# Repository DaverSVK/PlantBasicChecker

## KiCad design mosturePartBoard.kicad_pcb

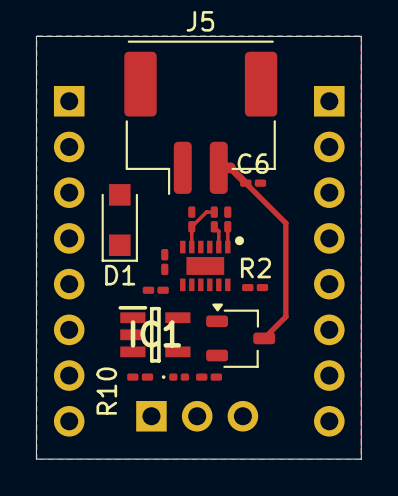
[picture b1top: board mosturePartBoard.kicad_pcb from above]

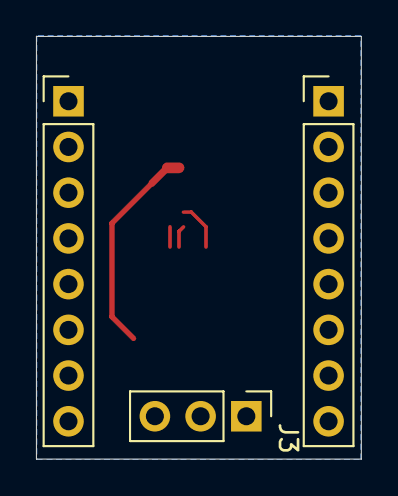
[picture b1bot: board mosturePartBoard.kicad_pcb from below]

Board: 2 copper layers, 18.1 x 23.5 mm, 18 parts (3 on the bottom side), 14 nets.

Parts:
C1, C2: C; C_0201_0603Metric_Pad0.64x0.40mm_HandSolder
C5, C6: 4u7; C_0201_0603Metric_Pad0.64x0.40mm_HandSolder
D1: PMEG2010ER; Nexperia_CFP3_SOD-123W
D3: LED; LED_0201_0603Metric
IC1: MCP73831T-2ACI_OT; SOT95P270X145-5N
J1, J2: Conn_01x08_Pin; PinHeader_1x08_P2.54mm_Vertical
J3: Conn_01x03_Pin; PinHeader_1x03_P2.54mm_Vertical
J5: Conn_01x02_Pin; Molex_CLIK-Mate_502443-0270_1x02-1MP_P2.00mm_Vertical
L1: L; L_0201_0603Metric_Pad0.64x0.40mm_HandSolder
PMV33UPE215: TSOT-23
PS1: TPS62740DSSR; TPS62740
R1: R; R_0201_0603Metric_Pad0.64x0.40mm_HandSolder
R2: 100k; R_0201_0603Metric_Pad0.64x0.40mm_HandSolder
R9: 2k; R_0201_0603Metric_Pad0.64x0.40mm_HandSolder
R10: 470; R_0201_0603Metric_Pad0.64x0.40mm_HandSolder

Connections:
ADC: J1.7, J3.3
CTRL_SENS: J2.8, PS1.4 (CTRL)
GND: C1.1, C2.2, C6.2, IC1.2 (VSS), J1.2, J3.1, J5.1, PS1.3 (GND), PS1.13 (EP), R2.1, R9.2
LOAD: J3.2, PS1.6 (LOAD)
MAIN_PWR: C2.1, J1.3, L1.1, PS1.5 (VOUT), R1.1
unnamed: C5.1, D3.2 (A), IC1.4 (VDD)
unnamed: D3.1 (K), R10.1
unnamed: IC1.5 (PROG), R9.1
unnamed: IC1.1 (STAT), R10.2
unnamed: PS1.7 (PG), R1.2
unnamed: L1.2, PS1.2 (SW)
VBAT: C6.1, IC1.3 (VBAT), J5.2, PMV33UPE215.3 (D)
VSYS: C1.2, D1.1 (K), PMV33UPE215.2 (S), PS1.1 (VIN), PS1.8 (VSEL4), PS1.9 (VSEL3), PS1.10 (VSEL2), PS1.11 (VSEL1), PS1.12 (EN)
VVCC: C5.2, D1.2 (A), J1.1, PMV33UPE215.1 (G), R2.2

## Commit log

2026-02-14 basic version
2026-04-07 need to edit powerlines
2026-04-13 restrusture
